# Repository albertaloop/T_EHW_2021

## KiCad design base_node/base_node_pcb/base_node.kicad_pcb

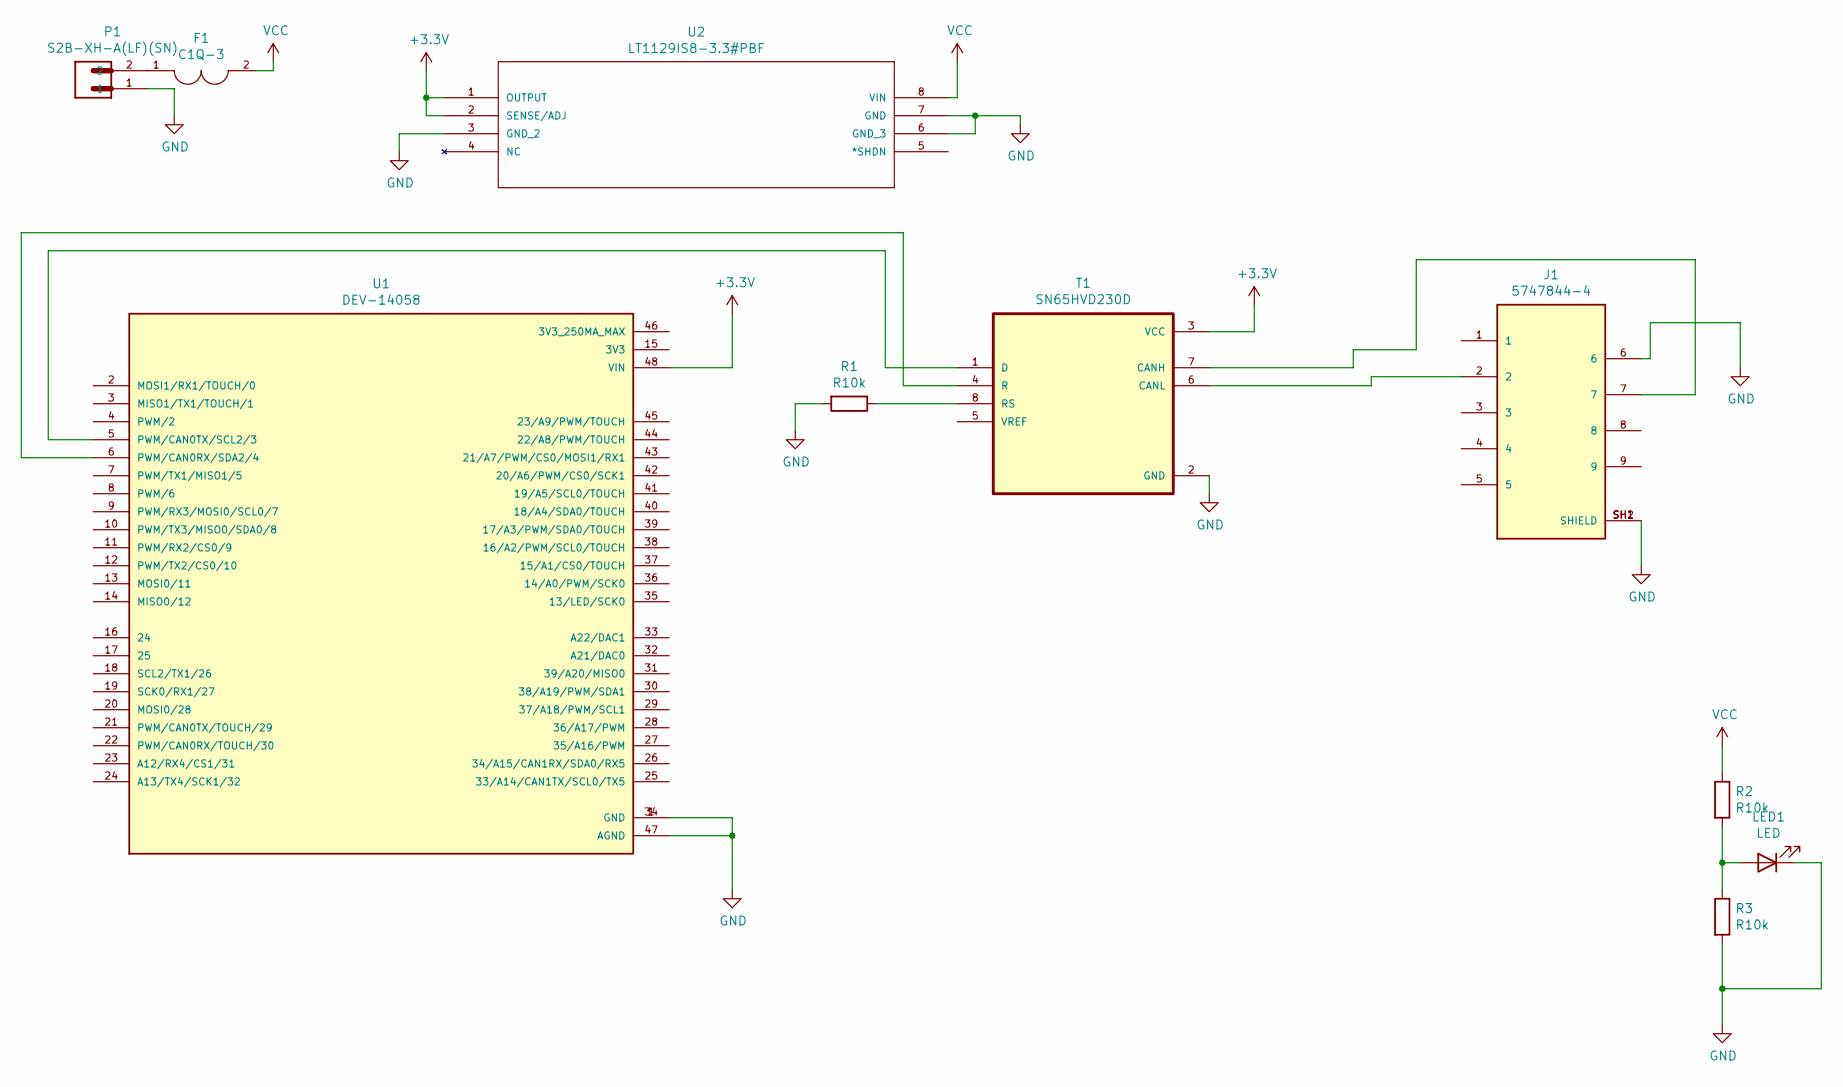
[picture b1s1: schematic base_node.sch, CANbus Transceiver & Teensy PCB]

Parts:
F1: C1Q-3; FUSC3215X78N; PARTREV Nov2018
J1: 5747844-4; TE_5747844-4
LED1: LED; LED_D4.0mm
P1: S2B-XH-A(LF)(SN); JST_S2B-XH-A(LF)(SN)
R1, R2, R3: R10k; R_1206_3216Metric
T1: SN65HVD230D; SOIC127P599X175-8N
U1: DEV-14058; MODULE_DEV-14058; PARTREV 3.6
U2: LT1129IS8-3.3#PBF; SO-8_S; MANUFACTURER_PART_NUMBER lt1129is85

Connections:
+3V3: T1.3 (VCC), U1.48 (VIN), U2.1 (OUTPUT), U2.2 (SENSE/ADJ)
GND: J1.6, J1.SH1 (SHIELD), J1.SH2 (SHIELD), LED1.1 (K), P1.1, R1.2, R3.2, T1.2 (GND), U1.1 (GND), U1.34 (GND), U1.47 (AGND), U2.3 (GND_2), U2.6 (GND_3), U2.7 (GND)
unnamed: F1.1, P1.2
unnamed: J1.2, T1.6 (CANL)
unnamed: J1.7, T1.7 (CANH)
unnamed: LED1.2 (A), R2.2, R3.1
unnamed: R1.1, T1.8 (RS)
unnamed: T1.1 (D), U1.5 (PWM/CAN0TX/SCL2/3)
unnamed: T1.4 (R), U1.6 (PWM/CAN0RX/SDA2/4)
VCC: F1.2, R2.1, U2.8 (VIN)

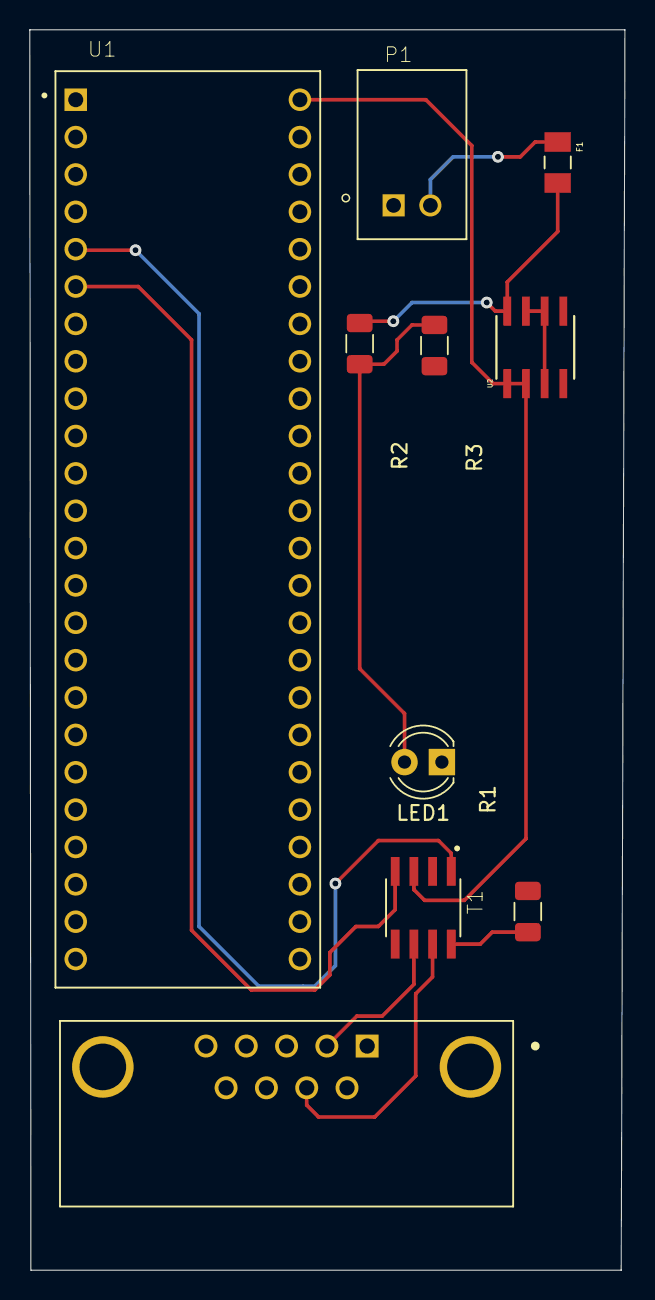
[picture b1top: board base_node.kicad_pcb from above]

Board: 2 copper layers, 40.5 x 84.3 mm, 10 parts (0 on the bottom side), 10 nets.

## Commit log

2021-01-14 init commit

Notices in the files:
base_node/base_node_pcb/base_node.kicad_pcb:
License:  -----
